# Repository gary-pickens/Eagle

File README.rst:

##########################################
House Monitor Schematics and board layouts.
##########################################

These are the schematics and board layouts for the House Monitor project. 

Gary Pickens

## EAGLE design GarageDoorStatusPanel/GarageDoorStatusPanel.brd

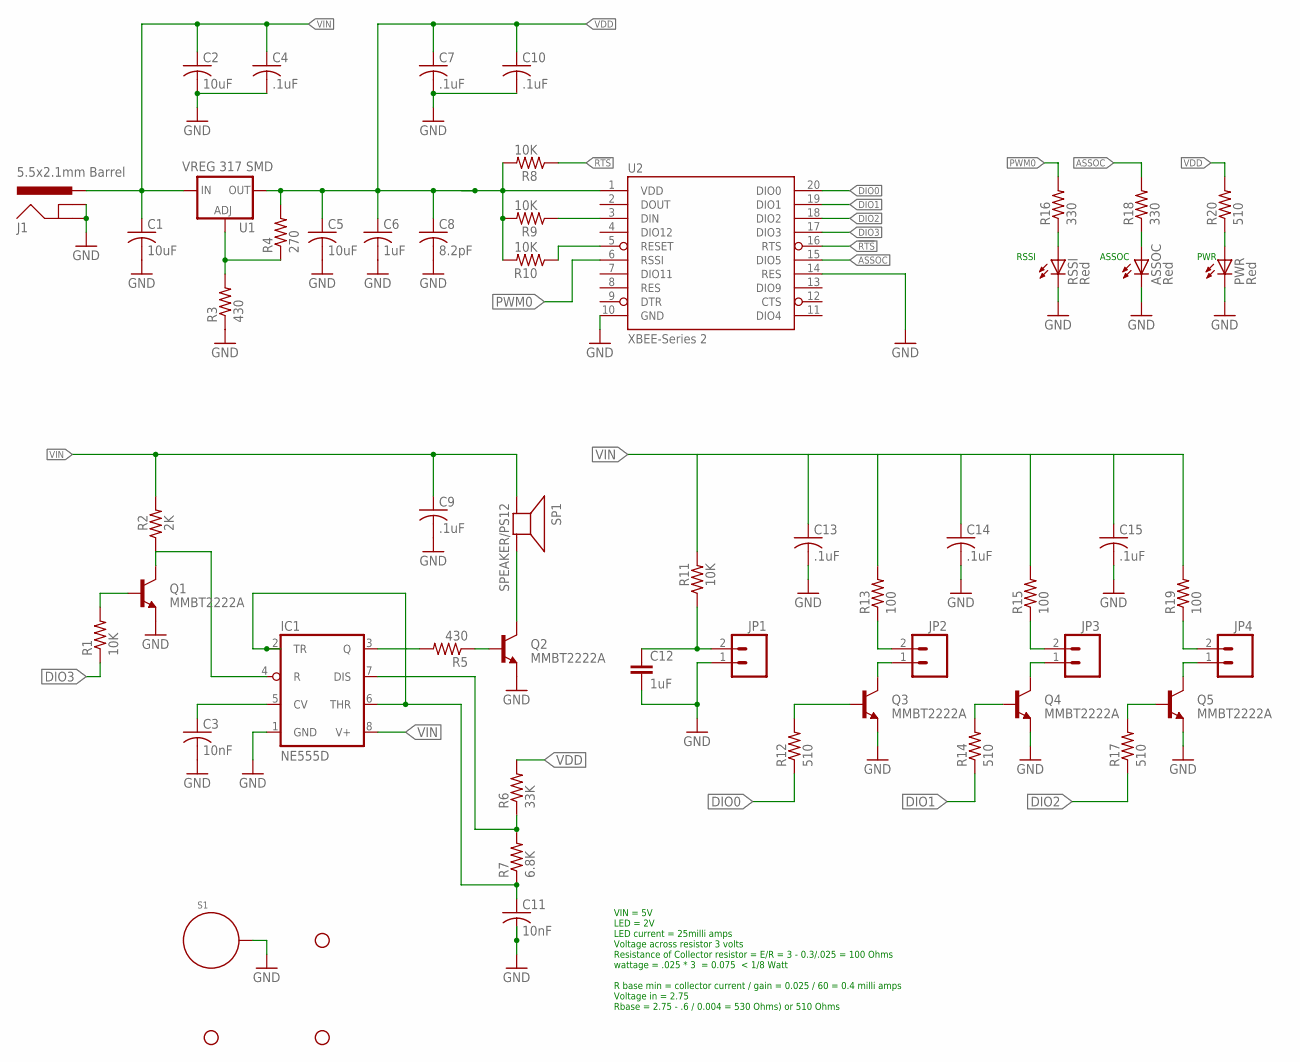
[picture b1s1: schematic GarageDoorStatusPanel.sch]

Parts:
ASSOC: Red; CHIP-LED0603
C1, C2, C5: 10uF; C0805
C3, C11: 10nF; C0805
C4, C7, C9, C10, C13, C14, C15: .1uF; C0805
C6: 1uF; C0805
C8: 8.2pF; C0805
C12: 1uF; 0603-CAP
IC1: NE555D; SO08; MPN NE555DR
J1: 5.5x2.1mm Barrel; POWER_JACK_SMD
JP1, JP2, JP3, JP4: M02POLAR_LOCK; MOLEX-1X2_LOCK
PWR: Red; CHIP-LED0603
Q1, Q2, Q3, Q4, Q5: MMBT2222A; SOT23; MPN MMBT4401
R1, R8, R9, R10, R11: 10K; R0805
R2: 2K; R0805
R3, R5: 430; R0805
R4: 270; R0805
R6: 33K; R0805
R7: 6.8K; R0805
R12, R14, R17, R20: 510; R0805
R13, R15, R19: 100; R0805
R16, R18: 330; R0805
RSSI: Red; CHIP-LED0603
S1: STANDOFF_ELECTRICAL; STANDOFF-ELECTRICAL
SP1: SPEAKER/PS12; PS12
STANDOFF1, STANDOFF2, STANDOFF3: STAND-OFF
U1: VREG 317 SMD; SOT223
U2: XBEE-Series 2; XBEE-SMD

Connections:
!RESET: R10.1, U2.5 (RESET)
!RTS: R8.1, U2.16 (RTS)
ASSOC: R18.2, U2.15 (DIO5)
DIN: R9.1, U2.3 (DIN)
DIO0: R12.1, U2.20 (DIO0)
DIO1: R14.1, U2.19 (DIO1)
DIO2: R17.1, U2.18 (DIO2)
DIO3: R1.1, U2.17 (DIO3)
DIO3?: C11.1, IC1.2 (TR), IC1.6 (THR), R7.1
GND: ASSOC.C, C1.2, C2.2, C3.2, C4.2, C5.2, C6.2, C7.2, C8.2, C9.2, C10.2, C11.2, C12.2, C13.2, C14.2, C15.2, IC1.1 (GND), J1.GND (GNDBREAK), J1.P$4 (GND), JP1.1, PWR.C, Q1.2 (E), Q2.2 (E), Q3.2 (E), Q4.2 (E), Q5.2 (E), R3.1, RSSI.C, S1.P1, U2.10 (GND), U2.14 (RES)
unnamed: IC1.3 (Q), R5.2
unnamed: Q2.1 (B), R5.1
unnamed: R3.2, R4.1, U1.1 (ADJ)
unnamed: Q2.3 (C), SP1.P$2 (-)
unnamed: C3.1, IC1.5 (CV)
unnamed: IC1.7 (DIS), R6.1, R7.2
unnamed: Q5.1 (B), R17.2
unnamed: Q4.1 (B), R14.2
unnamed: Q3.1 (B), R12.2
unnamed: JP3.2, R15.1
unnamed: JP3.1, Q4.3 (C)
unnamed: JP4.2, R19.1
unnamed: JP2.2, R13.1
unnamed: JP2.1, Q3.3 (C)
unnamed: JP4.1, Q5.3 (C)
unnamed: ASSOC.A, R18.1
unnamed: PWR.A, R20.1
unnamed: R16.1, RSSI.A
unnamed: C12.1, JP1.2, R11.1
unnamed: IC1.4 (R), Q1.3 (C), R2.1
unnamed: Q1.1 (B), R1.2
PWM0: R16.2, U2.6 (RSSI)
VDD: C5.1, C6.1, C7.1, C8.1, C10.1, R4.2, R6.2, R8.2, R9.2, R10.2, R20.2, U1.2 (OUT), U2.1 (VDD)
VIN: C1.1, C2.1, C4.1, C9.1, C13.1, C14.1, C15.1, IC1.8 (V+), J1.VIN0 (PWR), R2.2, R11.2, R15.2, R19.2, SP1.P$1 (+), U1.3 (IN)

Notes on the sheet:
ASSOC
PWR
RSSI
VIN = 5V LED = 2V LED current = 25milli amps Voltage across resistor 3 volts Resistance of Collector resistor = E/R = 3 - 0.3/.025 = 100 Ohms wattage = .025 * 3 = 0.075 < 1/8 Watt R base min = collector current / gain = 0.025 / 60 = 0.4 milli amps Voltage in = 2.75 Rbase = 2.75 - .6 / 0.004 = 530 O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

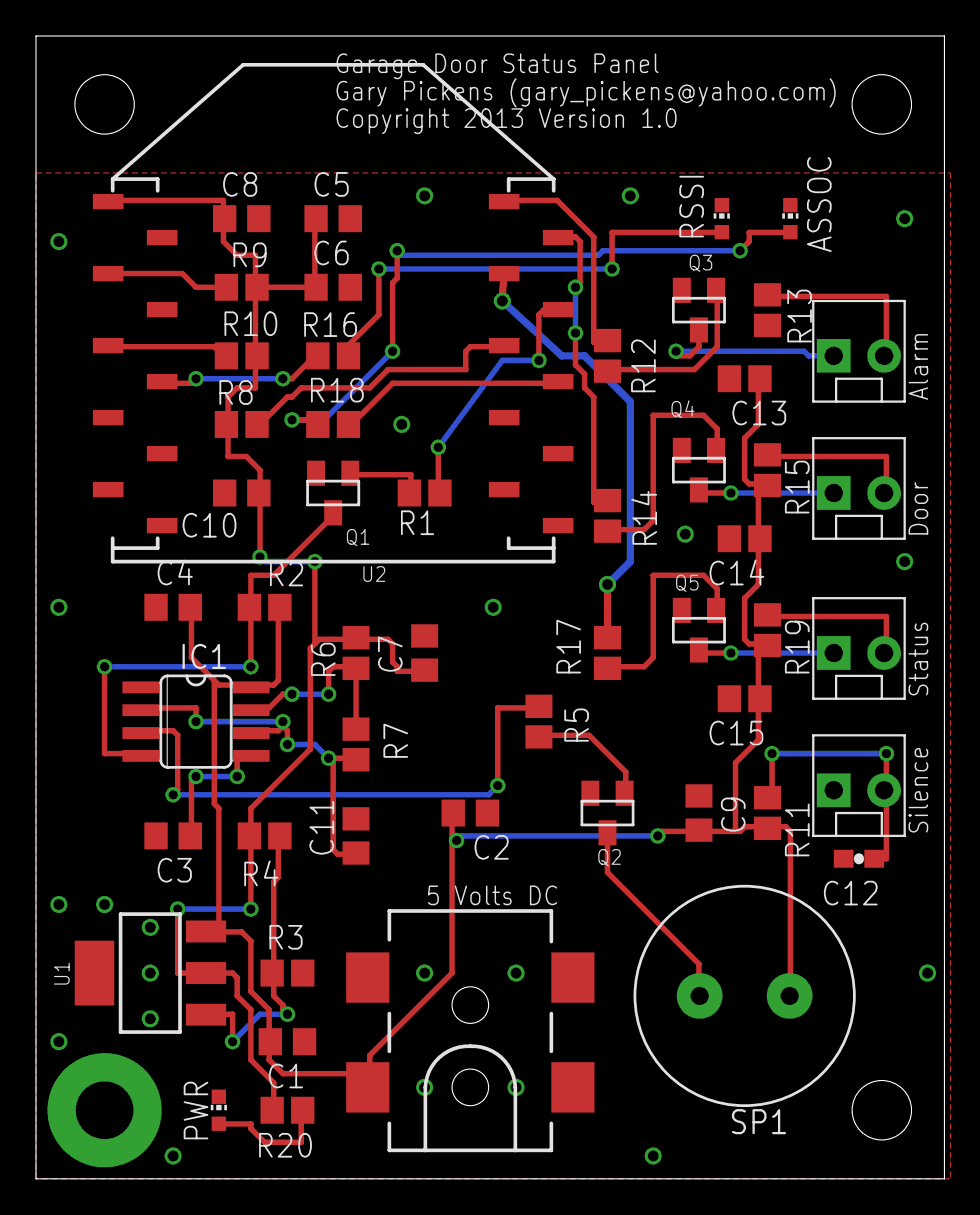
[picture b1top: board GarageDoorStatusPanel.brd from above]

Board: 2 copper layers, 50.5 x 63.5 mm, 56 parts (0 on the bottom side), 34 nets.

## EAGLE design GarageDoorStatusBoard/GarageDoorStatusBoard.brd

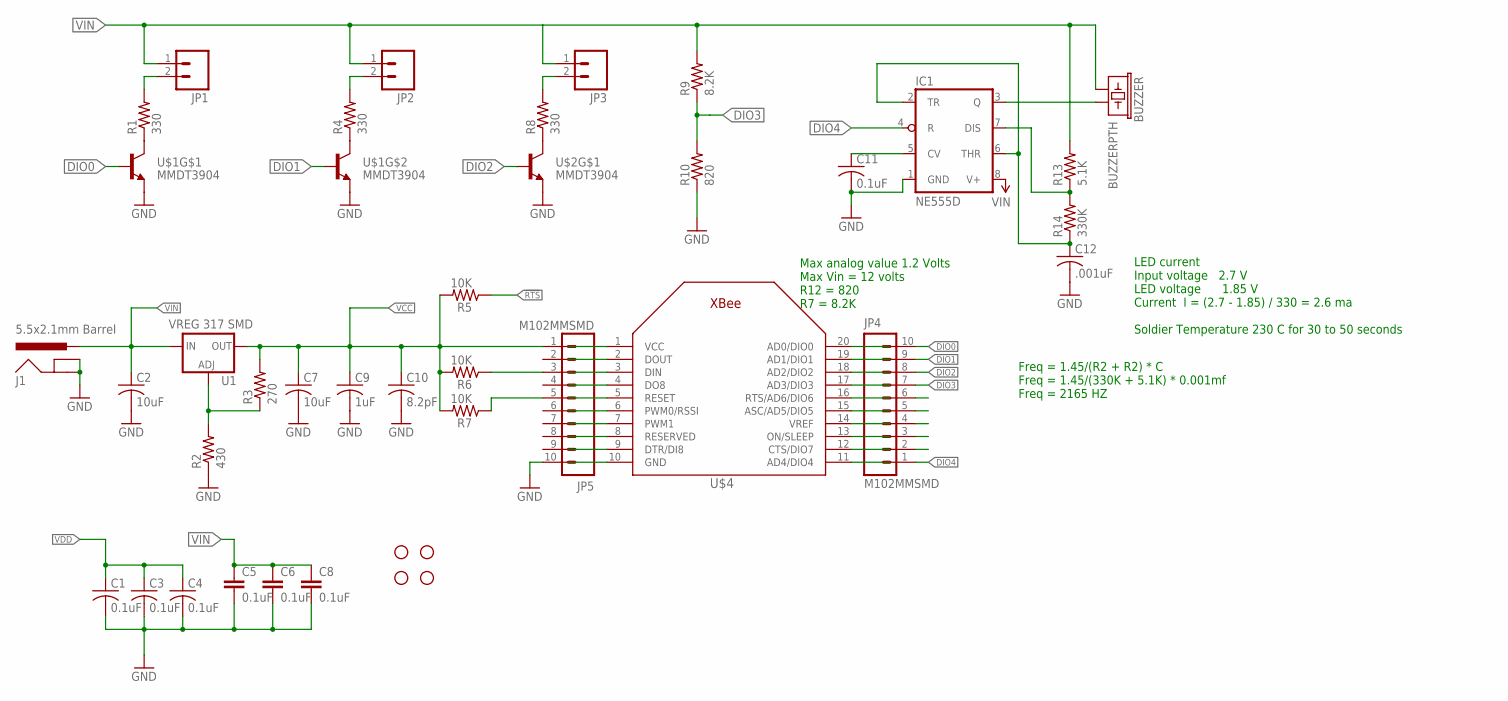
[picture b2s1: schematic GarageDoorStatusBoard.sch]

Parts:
BUZZER: BUZZERPTH; BUZZER-12MM
C1, C3, C4, C11: 0.1uF; C0805
C2, C7: 10uF; C0805
C5, C6, C8: 0.1uF; 0402-CAP
C9: 1uF; C0805
C10: 8.2pF; C0805
C12: .001uF; C0805
IC1: NE555D; SO08
J1: 5.5x2.1mm Barrel; POWER_JACK_SMD
JP1, JP2, JP3: M02POLAR_LOCK; MOLEX-1X2_LOCK
JP4, JP5: M102MMSMD; 1X10-2MM-SMD
R1, R4, R8: 330; R0805
R2: 430; R0805
R3: 270; R0805
R5, R6, R7: 10K; R0805
R9: 8.2K; 0805
R10: 820; 0805
R13: 5.1K; R0805
R14: 330K; R0805
STANDOFF1, STANDOFF2, STANDOFF3, STANDOFF4: STAND-OFF
U1: VREG 317 SMD; SOT223
U$1, U$2: MMDT3904; SOT363
U$4: XBEE

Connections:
!RESET: JP5.5, R7.1
!RTS: R5.1
DIO0: JP4.10, U$1.2 (B)
DIO1: JP4.9, U$1.5 (B)
DIO2: JP4.8, U$2.2 (B)
DIO3: JP4.7, R9.1, R10.2
DIO4: IC1.4 (R), JP4.1
GND: C1.2, C2.2, C3.2, C4.2, C5.2, C6.2, C7.2, C8.2, C9.2, C10.2, C11.2, C12.2, IC1.1 (GND), J1.GND (GNDBREAK), J1.P$4 (GND), JP5.10, R2.1, R10.1, U$1.1 (E), U$1.4 (E), U$2.1 (E), U$4.10 (GND)
unnamed: R1.1, U$1.6 (C)
unnamed: C12.1, IC1.2 (TR), IC1.6 (THR), R14.1
unnamed: R2.2, R3.1, U1.1 (ADJ)
unnamed: C11.1, IC1.5 (CV)
unnamed: R4.1, U$1.3 (C)
unnamed: JP2.2, R4.2
unnamed: R8.1, U$2.6 (C)
unnamed: JP1.2, R1.2
unnamed: JP3.2, R8.2
unnamed: BUZZER.- (2), IC1.3 (Q)
unnamed: IC1.7 (DIS), R13.1, R14.2
unnamed: JP5.3, R6.1
VCC: C7.1, C9.1, C10.1, JP5.1, R3.2, R5.2, R6.2, R7.2, U1.2 (OUT), U$4.1 (VCC)
VDD: C1.1, C3.1, C4.1
VIN: BUZZER.+ (1), C2.1, C5.1, C6.1, C8.1, IC1.8 (V+), J1.VIN0 (PWR), JP1.1, JP2.1, JP3.1, R9.2, R13.2, U1.3 (IN)

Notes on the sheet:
LED current Input voltage 2.7 V LED voltage 1.85 V Current I = (2.7 - 1.85) / 330 = 2.6 ma Soldier Temperature 230 C for 30 to 50 seconds
Freq = 1.45/(R2 + R2) * C Freq = 1.45/(330K + 5.1K) * 0.001mf Freq = 2165 HZ
Max analog value 1.2 Volts Max Vin = 12 volts R12 = 820 R7 = 8.2K

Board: 2 copper layers, 40 parts (0 on the bottom side), 22 nets, no tracks yet.

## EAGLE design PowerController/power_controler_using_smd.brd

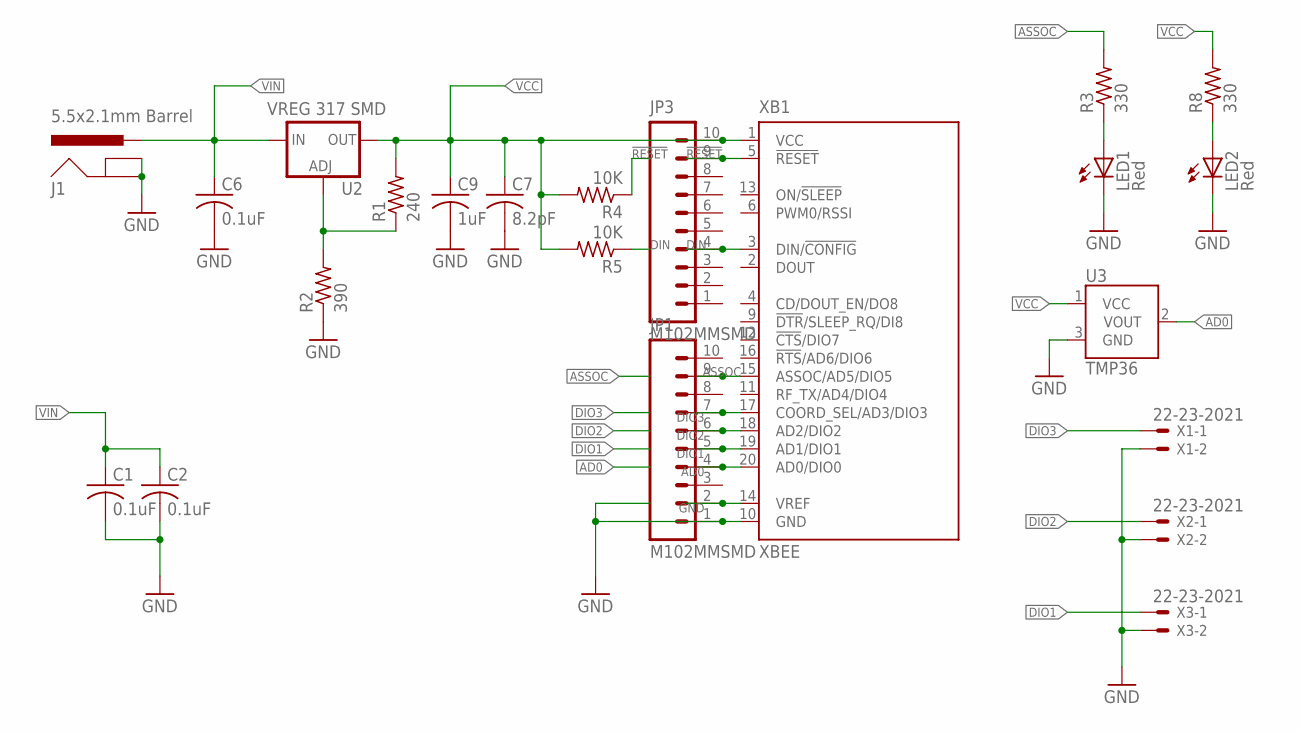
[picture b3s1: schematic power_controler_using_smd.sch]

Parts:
C1, C2, C6: 0.1uF; C0805
C7: 8.2pF; C0805
C9: 1uF; C0805
J1: 5.5x2.1mm Barrel; POWER_JACK_SMD
JP1, JP3: M102MMSMD; 1X10-2MM-SMD
LED1, LED2: Red; CHIP-LED0603
R1: 240; R0805
R2: 390; R0805
R3, R8: 330; R0805
R4, R5: 10K; R0805
U2: VREG 317 SMD; SOT223
U3: TMP36; TO-92
X1, X2, X3: 22-23-2021
XB1: XBEE

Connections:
!RESET: JP3.9, R4.1, XB1.5 (!RESET)
AD0: JP1.4, U3.2 (VOUT), XB1.20 (AD0/DIO0)
ASSOC: JP1.9, R3.2, XB1.15 (ASSOC/AD5/DIO5)
DIN: JP3.4, R5.1, XB1.3 (DIN/!CONFIG)
DIO1: JP1.5, X3.1, XB1.19 (AD1/DIO1)
DIO2: JP1.6, X2.1, XB1.18 (AD2/DIO2)
DIO3: JP1.7, X1.1, XB1.17 (COORD_SEL/AD3/DIO3)
GND: C1.2, C2.2, C6.2, C7.2, C9.2, J1.GND (GNDBREAK), J1.P$4 (GND), JP1.1, JP1.2, LED1.C, LED2.C, R2.1, U3.3 (GND), X1.2, X2.2, X3.2, XB1.10 (GND), XB1.14 (VREF)
unnamed: LED1.A, R3.1
unnamed: LED2.A, R8.1
unnamed: R1.1, R2.2, U2.1 (ADJ)
VCC: C7.1, C9.1, JP3.10, R1.2, R4.2, R5.2, R8.2, U2.2 (OUT), U3.1 (VCC), XB1.1 (VCC)
VIN: C1.1, C2.1, C6.1, J1.VIN0 (PWR), U2.3 (IN)

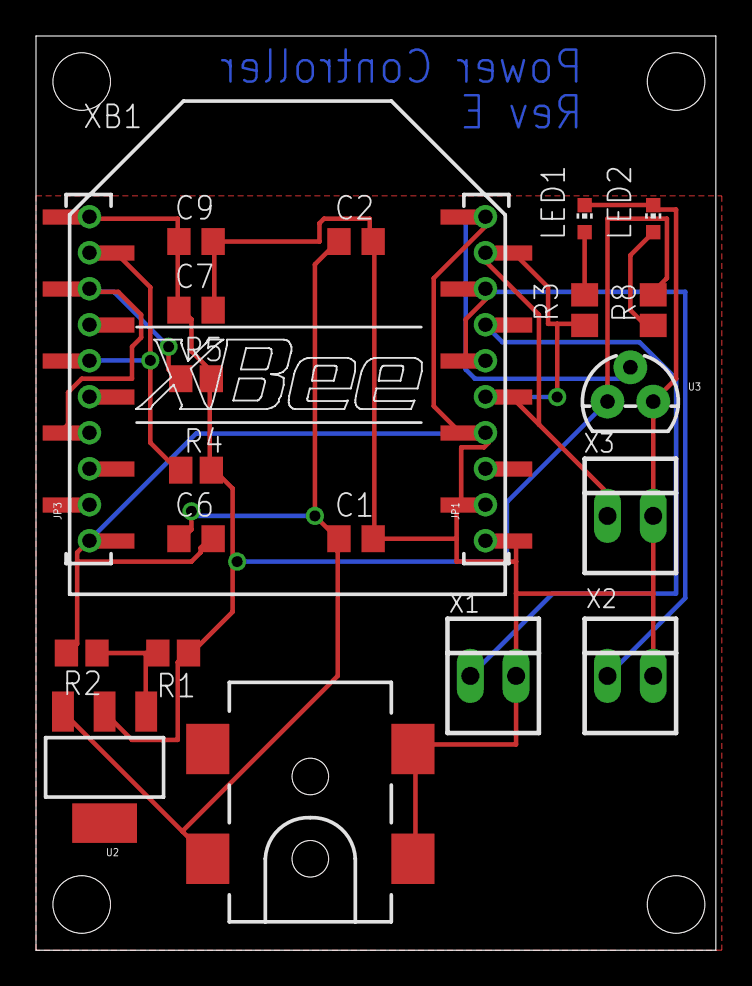
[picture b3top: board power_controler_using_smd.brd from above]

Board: 2 copper layers, 37.8 x 50.8 mm, 22 parts (0 on the bottom side), 13 nets.

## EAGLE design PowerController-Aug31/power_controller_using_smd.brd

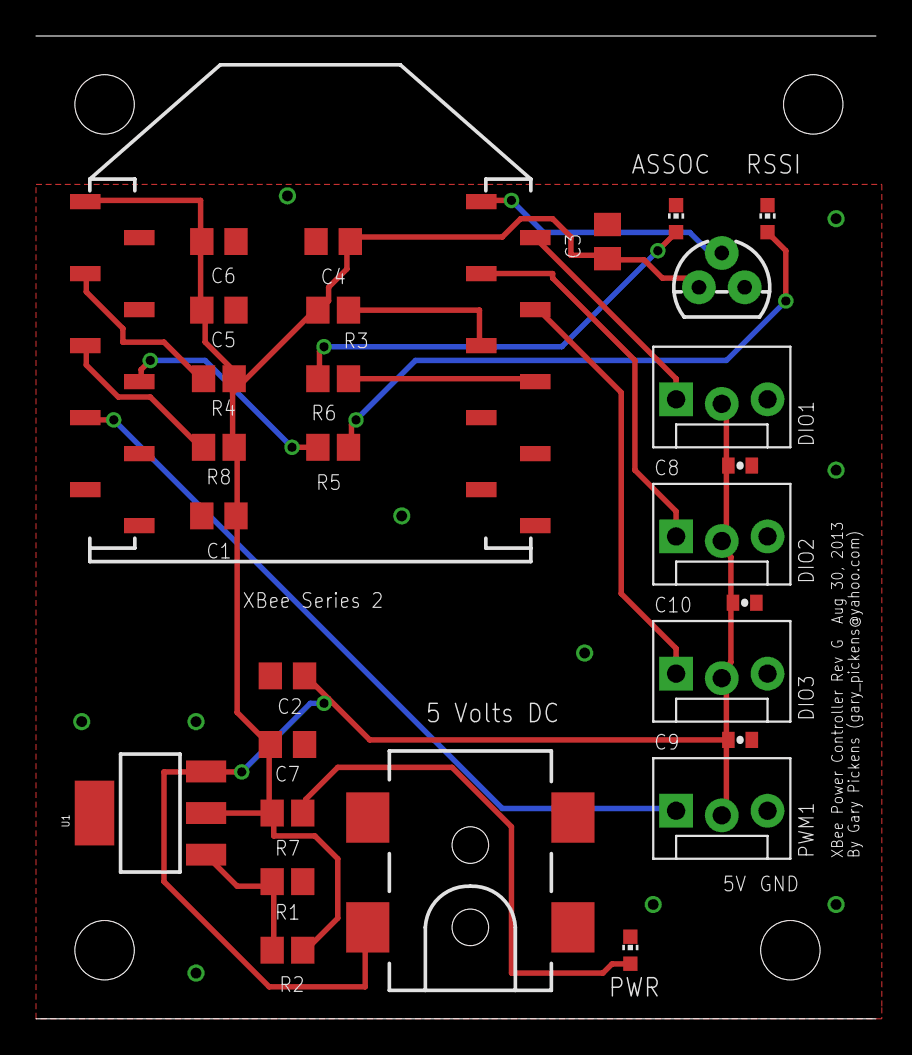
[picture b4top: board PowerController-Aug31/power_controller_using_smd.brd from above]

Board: 2 copper layers, 46.7 x 54.6 mm, 33 parts (0 on the bottom side), 17 nets.

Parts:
C1, C3, C7: 0.1uF; C0805
C2, C4: 10uF; C0805
C5: 1uF; C0805
C6: 8.2pF; C0805
C8, C9, C10: 0.1uF; 0402-CAP
J1: 5.5x2.1mm Barrel; POWER_JACK_SMD
LED1, LED2, LED3: Red; CHIP-LED0603
P1: DIO 1; MOLEX-1X3_LOCK
P2: DIO 2; MOLEX-1X3_LOCK
P3: DIO 3; MOLEX-1X3_LOCK
P4: PWM 1; MOLEX-1X3_LOCK
R1: 430; R0805
R2: 270; R0805
R3, R4, R8: 10K; R0805
R5, R6: 330; R0805
R7: 510; R0805
STANDOFF1, STANDOFF2, STANDOFF3, STANDOFF4: STAND-OFF
U1: VREG 317 SMD; SOT223
U2: TMP36; TO-92
U$1: XBEE-1B3; XBEE-SMD

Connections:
!RESET: R8.1, U$1.5
!RTS: R3.1, U$1.16
AD0: U2.2, U$1.20
ASSOC: R6.2, U$1.15
DIN: R4.1, U$1.3
DIO1: P1.1, U$1.19
DIO2: P2.1, U$1.18
DIO3: P3.1, U$1.17
GND: C1.2, C2.2, C3.2, C4.2, C5.2, C6.2, C7.2, C8.2, C9.2, C10.2, J1.GND, J1.P$4, LED1.C, LED2.C, LED3.C, P1.3, P2.3, P3.3, P4.3, R1.1, U2.3, U$1.10, U$1.14
unnamed: LED2.A, R6.1
unnamed: LED3.A, R7.1
unnamed: R1.2, R2.1, U1.1
unnamed: LED1.A, R5.1
PWM0: R5.2, U$1.6
PWM1: P4.1, U$1.7
VDD: C1.1, C3.1, C4.1, C5.1, C6.1, C7.1, R2.2, R3.2, R4.2, R7.2, R8.2, U1.2, U2.1, U$1.1
VIN: C2.1, C8.1, C9.1, C10.1, J1.VIN0, P1.2, P2.2, P3.2, P4.2, U1.3

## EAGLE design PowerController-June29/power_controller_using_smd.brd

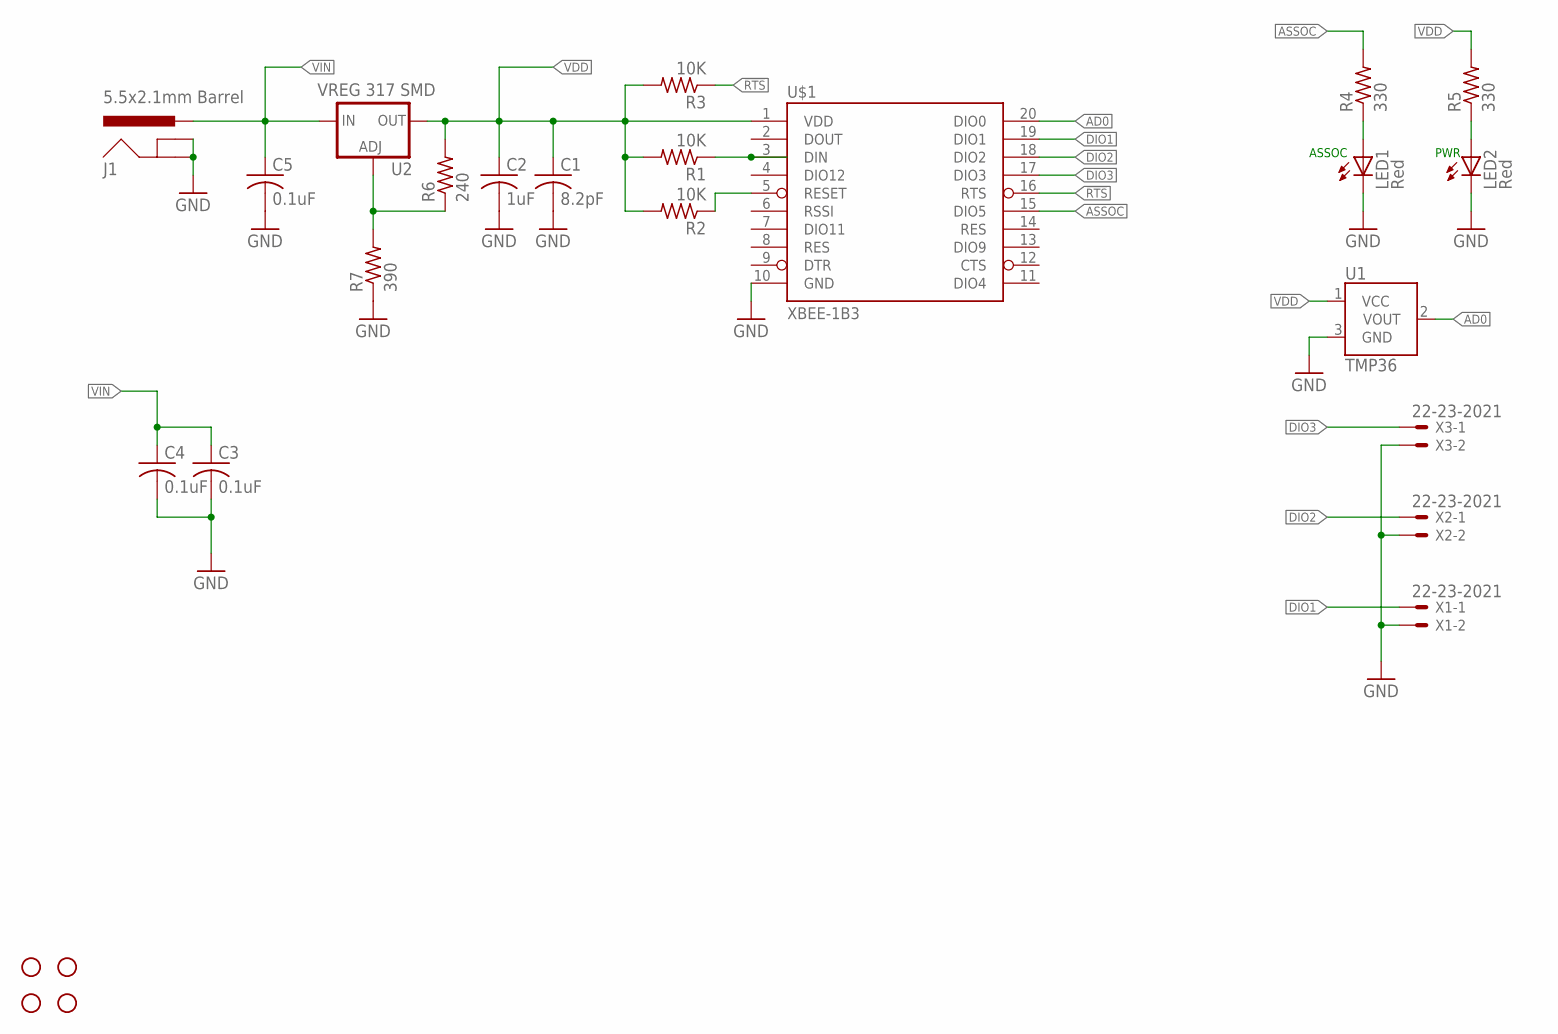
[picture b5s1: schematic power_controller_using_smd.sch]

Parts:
C1: 8.2pF; C0805
C2: 1uF; C0805
C3, C4, C5: 0.1uF; C0805
J1: 5.5x2.1mm Barrel; POWER_JACK_SMD
LED1, LED2: Red; CHIP-LED0603
R1, R2, R3: 10K; R0805
R4, R5: 330; R0805
R6: 240; R0805
R7: 390; R0805
STANDOFF1, STANDOFF2, STANDOFF3, STANDOFF4: STAND-OFF
U1: TMP36; TO-92
U2: VREG 317 SMD; SOT223
U$1: XBEE-1B3; XBEE-SMD
X1, X2, X3: 22-23-2021

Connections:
!RTS: R3.1, U$1.16 (RTS)
AD0: U1.2 (VOUT), U$1.20 (DIO0)
ASSOC: R4.2, U$1.15 (DIO5)
DIN: R1.1, U$1.3 (DIN)
DIO1: U$1.19 (DIO1), X1.1
DIO2: U$1.18 (DIO2), X2.1
DIO3: U$1.17 (DIO3), X3.1
GND: C1.2, C2.2, C3.2, C4.2, C5.2, J1.GND (GNDBREAK), J1.P$4 (GND), LED1.C, LED2.C, R7.1, U1.3 (GND), U$1.10 (GND), X1.2, X2.2, X3.2
unnamed: LED1.A, R4.1
unnamed: LED2.A, R5.1
unnamed: R6.1, R7.2, U2.1 (ADJ)
unnamed: R2.1, U$1.5 (RESET)
VDD: C1.1, C2.1, R1.2, R2.2, R3.2, R5.2, R6.2, U1.1 (VCC), U2.2 (OUT), U$1.1 (VDD)
VIN: C3.1, C4.1, C5.1, J1.VIN0 (PWR), U2.3 (IN)

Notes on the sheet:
ASSOC
PWR

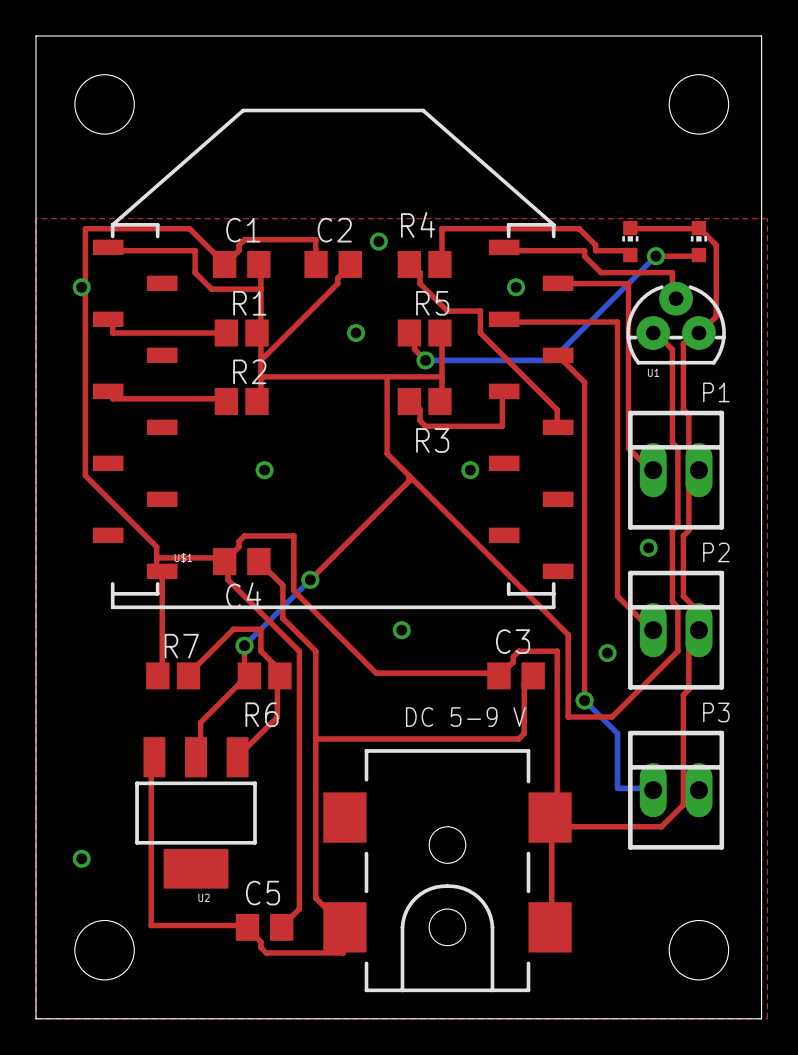
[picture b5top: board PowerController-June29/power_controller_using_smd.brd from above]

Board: 2 copper layers, 40.3 x 54.6 mm, 25 parts (0 on the bottom side), 14 nets.

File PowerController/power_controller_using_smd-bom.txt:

Partlist exported from C:/Users/Gary/eagle/PowerController/power_controller_using_smd.sch at 6/29/2013 3:29:46 PM

Part      Value            Device          Package        Description                            MF    MPN        OC_FARNELL OC_NEWARK PROD_ID    VALUE           
C1        8.2pF            C-USC0805       C0805          CAPACITOR, American symbol                                                                              
C2        1uF              C-USC0805       C0805          CAPACITOR, American symbol                                                                              
C3        0.1uF            C-USC0805       C0805          CAPACITOR, American symbol                                                                              
C4        0.1uF            C-USC0805       C0805          CAPACITOR, American symbol                                                                              
C5        0.1uF            C-USC0805       C0805          CAPACITOR, American symbol                                                                              
J1        5.5x2.1mm Barrel POWER_JACKSMD   POWER_JACK_SMD Power Jack                                                                   CONN-08106 5.5x2.1mm Barrel
LED1      Red              LEDCHIP-LED0603 CHIP-LED0603   LED                                                                                                     
LED2      Red              LEDCHIP-LED0603 CHIP-LED0603   LED                                                                                                     
R1        10K              R-US_R0805      R0805          RESISTOR, American symbol                                                                               
R2        10K              R-US_R0805      R0805          RESISTOR, American symbol                                                                               
R3        10K              R-US_R0805      R0805          RESISTOR, American symbol                                                                               
R4        330              R-US_R0805      R0805          RESISTOR, American symbol                                                                               
R5        330              R-US_R0805      R0805          RESISTOR, American symbol                                                                               
R6        240              R-US_R0805      R0805          RESISTOR, American symbol                                                                               
R7        390              R-US_R0805      R0805          RESISTOR, American symbol                                                                               
STANDOFF1 STAND-OFF        STAND-OFF       STAND-OFF      #4 Stand Off                                                                                            
STANDOFF2 STAND-OFF        STAND-OFF       STAND-OFF      #4 Stand Off                                                                                            
STANDOFF3 STAND-OFF        STAND-OFF       STAND-OFF      #4 Stand Off                                                                                            
STANDOFF4 STAND-OFF        STAND-OFF       STAND-OFF      #4 Stand Off                                                                                            
U$1       XBEE-1B3         XBEE-1B3        XBEE-SMD       Xbee module footprints                                                       CONN-09042                 
U1        TMP36            TMP36GT9        TO-92          Precision degC temp sensor, analog out                                                                  
U2        VREG 317 SMD     V_REG_317SMD    SOT223         Voltage Regulator                                                                                       
X1        22-23-2021       22-23-2021      22-23-2021     .100" (2.54mm) Center Header - 2 Pin   MOLEX 22-23-2021 1462926    25C3832                              
X2        22-23-2021       22-23-2021      22-23-2021     .100" (2.54mm) Center Header - 2 Pin   MOLEX 22-23-2021 1462926    25C3832                              
X3        22-23-2021       22-23-2021      22-23-2021     .100" (2.54mm) Center Header - 2 Pin   MOLEX 22-23-2021 1462926    25C3832

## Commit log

2013-09-05 starting a new respository, first file.
2013-09-09 Putting these boards in GIT
2013-09-09 Adding a README file
2013-09-09 Updating the documentation
2013-09-09 First iteration of Garage Door Status Board
2013-09-10 More work on the Garage Door Status Panel.
2013-09-10 More files to ignore
2013-09-16 Started work on Garage Door Status Board
2013-09-17 Add a Eagle library with some of the things I use a lot and are hard to find.
2013-09-17 Some more cleanup
2013-09-23 Adding a new PCB: Garage Door Status Panel
2013-09-23 Added gitignore
2013-09-24 These boards are real close to the final version. I want to try it with some larger traces.
2013-09-24 Everything is ready to go.
2013-09-24 Final
2013-09-24 More files to check in before sending off the order.

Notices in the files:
GarageDoorStatusPanel/GarageDoorStatusPanel.brd:
Copyright 2013 Version 1.0
parts and their libraries:
SparkFun-Connectors: Licensing: CC v3.0 Share-Alike You are welcome to use this library for commercial purposes.
